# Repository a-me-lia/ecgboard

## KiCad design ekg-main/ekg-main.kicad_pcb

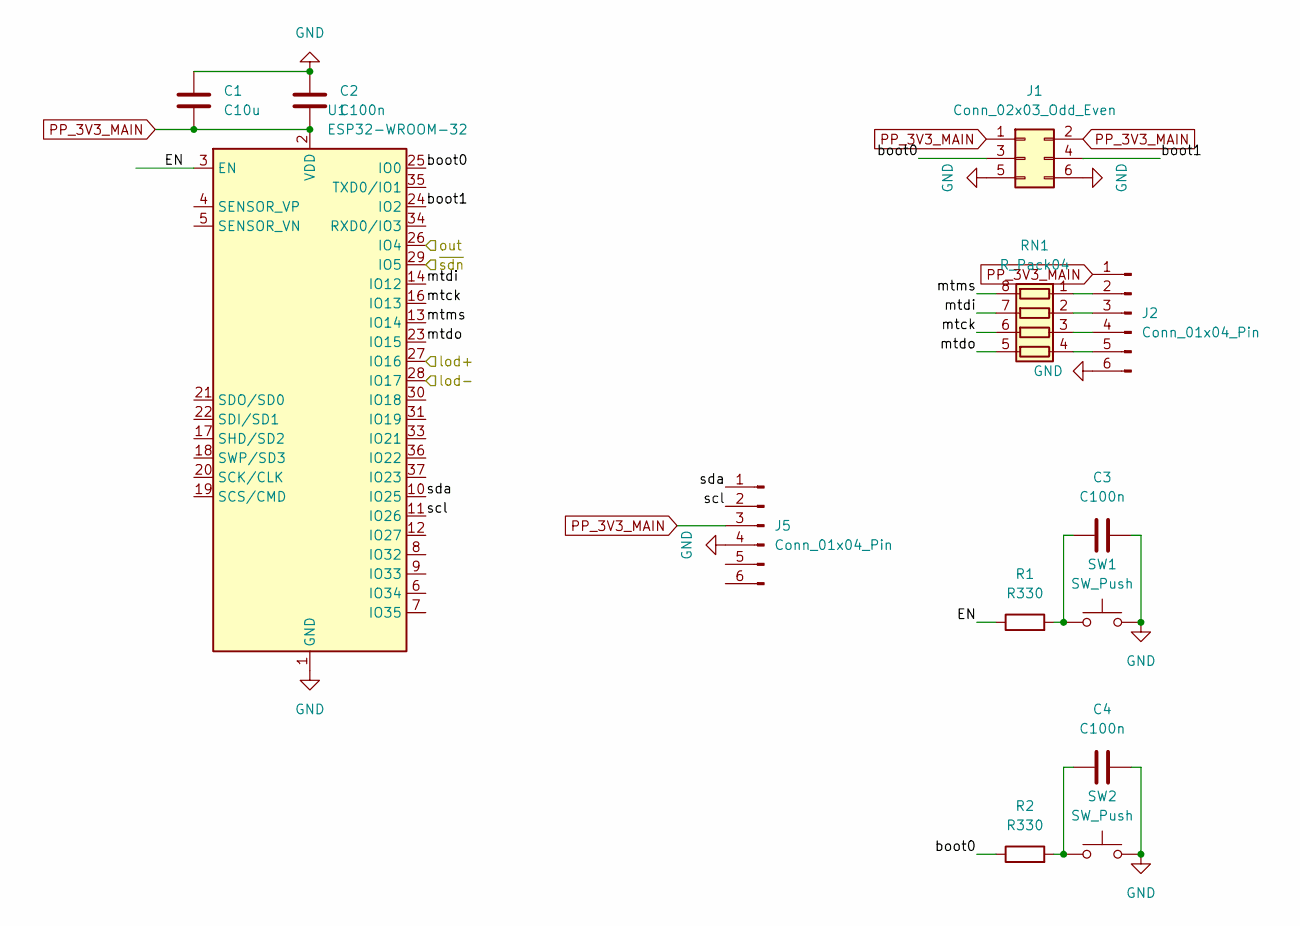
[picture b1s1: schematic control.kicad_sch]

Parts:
C1: C10u; C_0402_1005Metric; LCSC C15525
C2, C3, C4: C100n; C_0402_1005Metric; LCSC C60474
J1: Conn_02x03_Odd_Even; PinHeader_2x03_P2.54mm_Vertical_SMD; LCSC C192301
J2, J5: Conn_01x04_Pin; PinHeader_1x06_P2.54mm_Vertical_SMD_Pin1Left; LCSC C2883763
R1, R2: R330; C_0402_1005Metric; LCSC C12246
RN1: R_Pack04; R_Array_Concave_4x0603; LCSC C29719
SW1, SW2: SW_Push; SW_SPST_B3SL-1022P; LCSC C86708
U1: ESP32-WROOM-32; LCSC C82899

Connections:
/control/EN: R1.1, U1.3 (EN)
/control/boot0: J1.3, R2.1, U1.25 (IO0)
/control/boot1: J1.4, U1.24 (IO2)
/control/lod+: U1.27 (IO16); also elsewhere on the board
/control/lod-: U1.28 (IO17); also elsewhere on the board
/control/mtck: RN1.6 (R3.2), U1.16 (IO13)
/control/mtdi: RN1.7 (R2.2), U1.14 (IO12)
/control/mtdo: RN1.5 (R4.2), U1.23 (IO15)
/control/mtms: RN1.8 (R1.2), U1.13 (IO14)
/control/scl: J5.2, U1.11 (IO26)
/control/sda: J5.1, U1.10 (IO25)
/control/~sdn: U1.29 (IO5); also elsewhere on the board
/ekg/out: U1.26 (IO4); also elsewhere on the board
GND: C1.1, C2.1, C3.2, C4.2, J1.5, J1.6, J2.6, J5.4, SW1.2, SW2.2, U1.1 (GND), U1.15 (GND), U1.38 (GND), U1.39 (GND); also elsewhere on the board
unnamed: C3.1, R1.2, SW1.1
unnamed: C4.1, R2.2, SW2.1
unnamed: J2.2, RN1.1 (R1.1)
unnamed: J2.3, RN1.2 (R2.1)
unnamed: J2.4, RN1.3 (R3.1)
unnamed: J2.5, RN1.4 (R4.1)
PP_3V3_MAIN: C1.2, C2.2, J1.1, J1.2, J2.1, J5.3, U1.2 (VDD); also elsewhere on the board

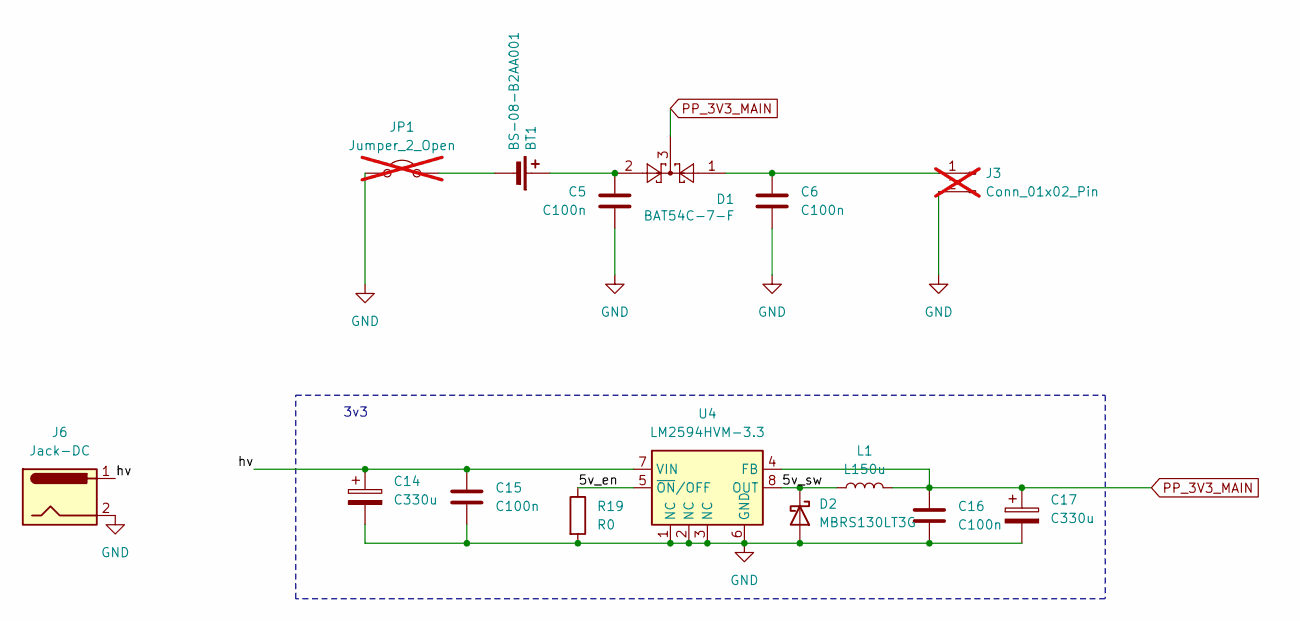
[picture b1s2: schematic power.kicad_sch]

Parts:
BT1: BS-08-B2AA001; LCSC C964777
C5, C6, C15, C16: C100n; C_0402_1005Metric; LCSC C60474
C14, C17: C330u; CP_Elec_6.3x7.7; LCSC C7461238
D1: BAT54C-7-F; SOT-23; LCSC C556168
D2: MBRS130LT3G; D_SMB; LCSC C51771
J3: Conn_01x02_Pin; PinHeader_1x02_P2.54mm_Vertical; not fitted
J6: Jack-DC; BarrelJack_Horizontal; LCSC C16214
JP1: Jumper_2_Open; PinSocket_1x02_P2.54mm_Vertical; not fitted
L1: L150u; L_Changjiang_FNR6045S; LCSC C168097
R19: R0; R_0402_1005Metric; LCSC C17168
U4: LM2594HVM-3.3; SOIC-8_3.9x4.9mm_P1.27mm; LCSC C18057294

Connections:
/power/5v_en: R19.1, U4.5 (~ON/OFF)
/power/5v_sw: D2.1 (K), L1.1, U4.8 (OUT)
/power/hv: C14.1, C15.1, J6.1, U4.7 (VIN)
GND: C5.2, C6.2, C14.2, C15.2, C16.2, C17.2, D2.2 (A), J3.2, J6.2, JP1.1 (A), R19.2, U4.1 (NC), U4.2 (NC), U4.3 (NC), U4.6 (GND); also elsewhere on the board
unnamed: BT1.+, C5.1, D1.2
unnamed: C6.1, D1.1, J3.1
unnamed: BT1.-, JP1.2 (B)
PP_3V3_MAIN: C16.1, C17.1, D1.3, L1.2, U4.4 (FB); also elsewhere on the board

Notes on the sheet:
3v3

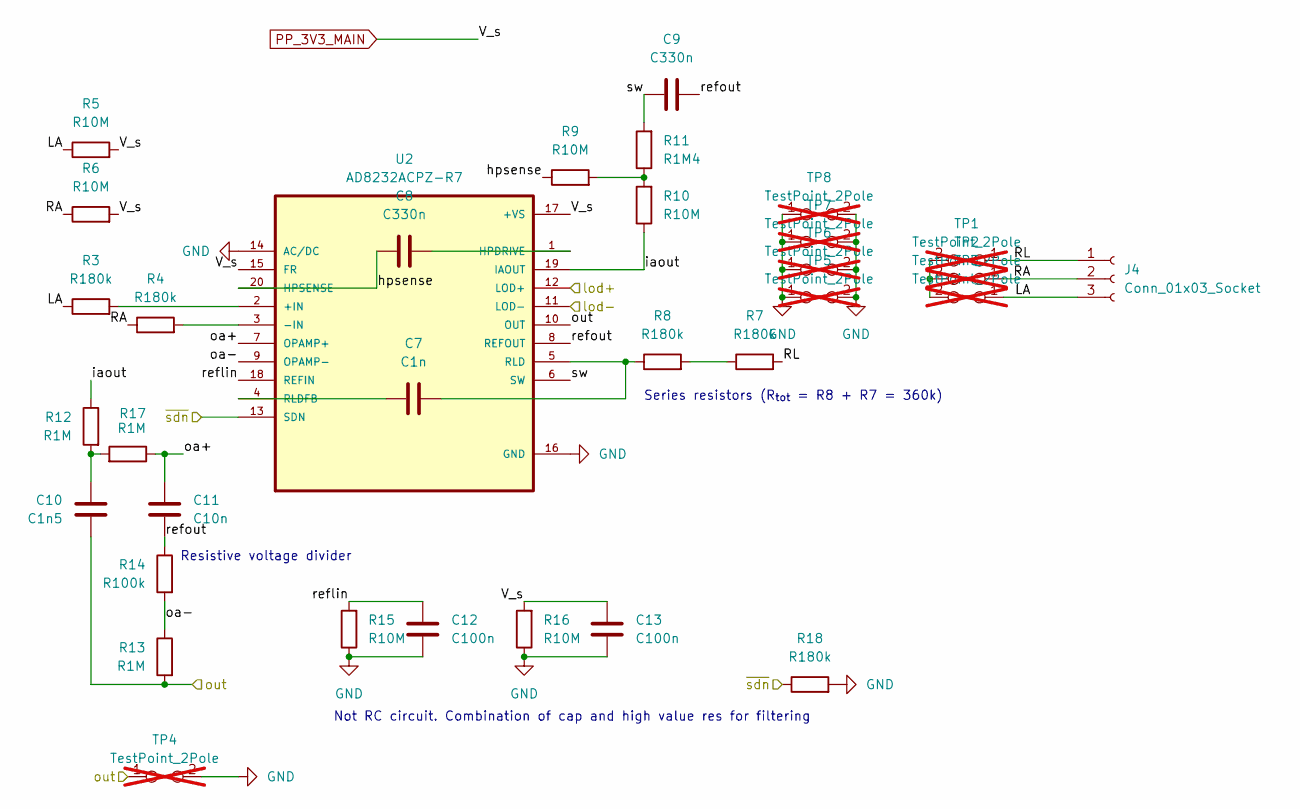
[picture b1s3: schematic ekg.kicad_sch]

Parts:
C7: C1n; C_0402_1005Metric; LCSC C106205
C8, C9: C330n; C_0402_1005Metric; LCSC C107013
C10: C1n5; C_0402_1005Metric; LCSC C107022
C11: C10n; C_0402_1005Metric; LCSC C60133
C12, C13: C100n; C_0402_1005Metric; LCSC C60474
J4: Conn_01x03_Socket; Molex_Micro-Fit_3.0_43650-0300_1x03_P3.00mm_Horizontal; LCSC C503478
R3, R4, R7, R8, R18: R180k; R_0402_1005Metric; LCSC C138046
R5, R6, R9, R10, R15, R16: R10M; R_0402_1005Metric; LCSC C138067
R11: R1M4; R_0402_1005Metric; LCSC C270644
R12, R13, R17: R1M; R_0402_1005Metric; LCSC C138033
R14: R100k; R_0402_1005Metric; LCSC C60491
TP1, TP2, TP3, TP4, TP5, TP6, TP7, TP8: TestPoint_2Pole; TestPoint_Bridge_Pitch2.54mm_Drill0.7mm; not fitted
U2: AD8232ACPZ-R7; QFN50P400X400X100-21N; LCSC C43216

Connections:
/control/lod+: U2.12 (LOD+); also elsewhere on the board
/control/lod-: U2.11 (LOD-); also elsewhere on the board
/control/~sdn: R18.1, U2.13 (SDN); also elsewhere on the board
/ekg/LA: J4.3, R3.1, R5.1, TP3.1
/ekg/RA: J4.2, R4.1, R6.1, TP2.1
/ekg/RL: J4.1, R7.2, TP1.1
/ekg/hpsense: C8.2, R9.1, U2.20 (HPSENSE)
/ekg/iaout: R10.1, R12.1, U2.19 (IAOUT)
/ekg/oa+: C11.1, R17.1, U2.7 (OPAMP+)
/ekg/oa-: R13.1, R14.2, U2.9 (OPAMP-)
/ekg/out: C10.2, R13.2, TP4.1, U2.10 (OUT); also elsewhere on the board
/ekg/reflin: C12.1, R15.2, U2.18 (REFIN)
/ekg/refout: C9.1, C11.2, R14.1, U2.8 (REFOUT)
/ekg/sw: C9.2, R11.2, U2.6 (SW)
GND: C12.2, C13.2, R15.1, R16.1, R18.2, TP4.2, TP5.1, TP5.2, TP6.1, TP6.2, TP7.1, TP7.2, TP8.1, TP8.2, U2.14 (AC/DC), U2.16 (GND); also elsewhere on the board
unnamed: C10.1, R12.2, R17.2
unnamed: R7.1, R8.2
unnamed: R9.2, R10.2, R11.1
unnamed: R3.2, U2.2 (+IN)
unnamed: R4.2, U2.3 (-IN)
unnamed: C8.1, U2.1 (HPDRIVE)
unnamed: C7.2, R8.1, U2.5 (RLD)
unnamed: C7.1, U2.4 (RLDFB)
PP_3V3_MAIN: C13.1, R5.2, R6.2, R16.2, U2.15 (FR), U2.17 (+VS); also elsewhere on the board

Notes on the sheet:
Not RC circuit. Combination of cap and high value res for filtering
Series resistors (R_{tot} = R8 + R7 = 360k)
Resistive voltage divider

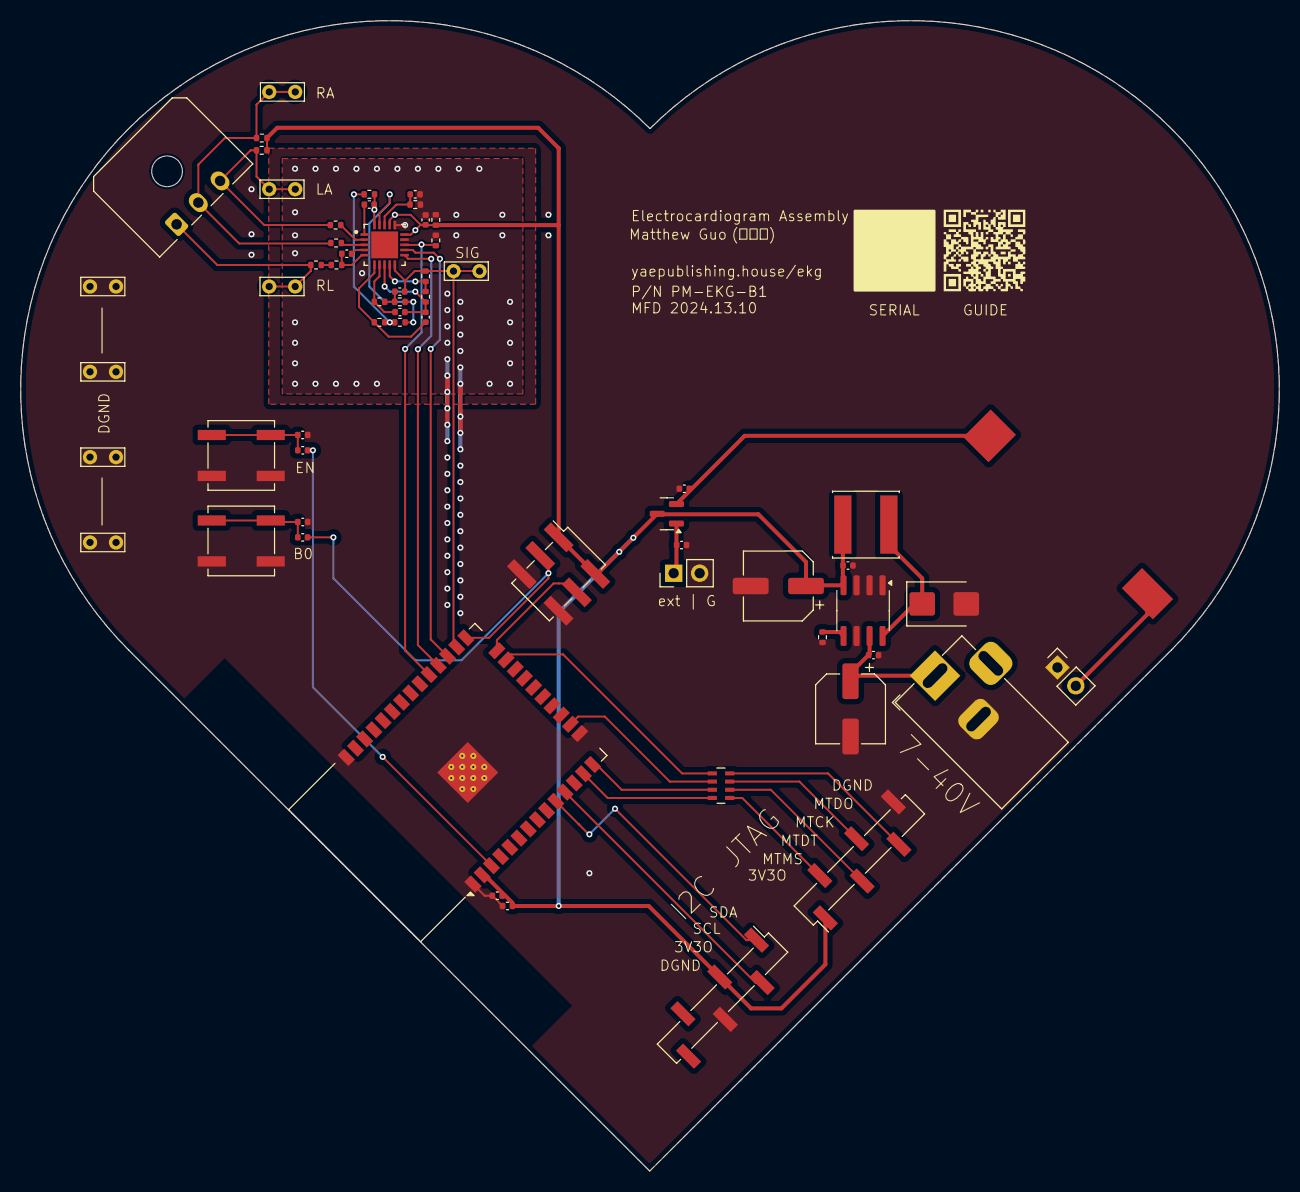
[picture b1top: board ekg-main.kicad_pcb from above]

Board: 2 copper layers, 122.9 x 112.3 mm, 61 parts (0 on the bottom side), 45 nets.

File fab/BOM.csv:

"Reference","Value","Datasheet","Footprint","Qty","DNP","LCSC"
"BT1","BS-08-B2AA001","https://www.keyelco.com/userAssets/file/M65p9.pdf","aaafootlib:BS-08-B2AA001","1","","C964777"
"C1","C10u","~","Capacitor_SMD:C_0402_1005Metric","1",""," C15525"
"C2,C3,C4,C5,C6,C12,C13,C15,C16","C100n","~","Capacitor_SMD:C_0402_1005Metric","9","","C60474"
"C7","C1n","~","Capacitor_SMD:C_0402_1005Metric","1","","C106205"
"C8,C9","C330n","~","Capacitor_SMD:C_0402_1005Metric","2","","C107013"
"C10","C1n5","~","Capacitor_SMD:C_0402_1005Metric","1","","C107022"
"C11","C10n","~","Capacitor_SMD:C_0402_1005Metric","1","","C60133"
"C14,C17","C330u","~","Capacitor_SMD:CP_Elec_6.3x7.7","2","","C7461238"
"D1","BAT54C-7-F","http://www.farnell.com/datasheets/2861240.pdf?_ga=2.12983117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","Package_TO_SOT_SMD:SOT-23","1","","C556168"
"D2","MBRS130LT3G","~","Diode_SMD:D_SMB","1","","C51771"
"J1","Conn_02x03_Odd_Even","~","Connector_PinHeader_2.54mm:PinHeader_2x03_P2.54mm_Vertical_SMD","1","","C192301"
"J2,J5","Conn_01x04_Pin","~","Connector_PinHeader_2.54mm:PinHeader_1x06_P2.54mm_Vertical_SMD_Pin1Left","2","","C2883763"
"J3","Conn_01x02_Pin","~","Connector_PinHeader_2.54mm:PinHeader_1x02_P2.54mm_Vertical","1","DNP",""
"J4","Conn_01x03_Socket","~","Connector_Molex:Molex_Micro-Fit_3.0_43650-0300_1x03_P3.00mm_Horizontal","1","","C503478"
"J6","Jack-DC","~","Connector_BarrelJack:BarrelJack_Horizontal","1","","C16214"
"JP1","Jumper_2_Open","~","Connector_PinSocket_2.54mm:PinSocket_1x02_P2.54mm_Vertical","1","DNP",""
"L1","L150u","https://www.lcsc.com/datasheet/lcsc_datasheet_2304140030_cji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","Inductor_SMD:L_Changjiang_FNR6045S","1","","C168097"
"R1,R2","R330","~","Capacitor_SMD:C_0402_1005Metric","2","","C12246"
"R3,R4,R7,R8,R18","R180k","~","Resistor_SMD:R_0402_1005Metric","5","","C138046"
"R5,R6,R9,R10,R15,R16","R10M","~","Resistor_SMD:R_0402_1005Metric","6","","C138067"
"R11","R1M4","~","Resistor_SMD:R_0402_1005Metric","1","","C270644"
"R12,R13,R17","R1M","~","Resistor_SMD:R_0402_1005Metric","3","","C138033"
"R14","R100k","~","Resistor_SMD:R_0402_1005Metric","1","","C60491"
"R19","R0","~","Resistor_SMD:R_0402_1005Metric","1",""," C17168"
"RN1","R_Pack04","~","Resistor_SMD:R_Array_Concave_4x0603","1","","C29719"
"SW1,SW2","SW_Push","~","Button_Switch_SMD:SW_SPST_B3SL-1022P","2","","C86708"
"TP1,TP2,TP3,TP4,TP5,TP6,TP7,TP8","TestPoint_2Pole","~","TestPoint:TestPoint_Bridge_Pitch2.54mm_Drill0.7mm","8","DNP",""
"U1","ESP32-WROOM-32","https://www.espressif.com/sites/default/files/documentation/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","RF_Module:ESP32-WROOM-32","1",""," C82899"
"U2","AD8232ACPZ-R7","","aaafootlib:QFN50P400X400X100-21N","1","","C43216"
"U4","LM2594HVM-3.3","http://www.ti.com/lit/ds/symlink/lm2594.pdf","Package_SO:SOIC-8_3.9x4.9mm_P1.27mm","1","","C18057294"

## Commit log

2024-12-16 fab1
